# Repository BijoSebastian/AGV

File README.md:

# AGV
Codes for autonomous navigation of ROVER 5 using Beaglebone Black
All modules are written as ROS nodes. PCB design for Beaglebone Black is also provided.
For additional details refer to https://bijosebastian.wordpress.com/mobile-robotics/

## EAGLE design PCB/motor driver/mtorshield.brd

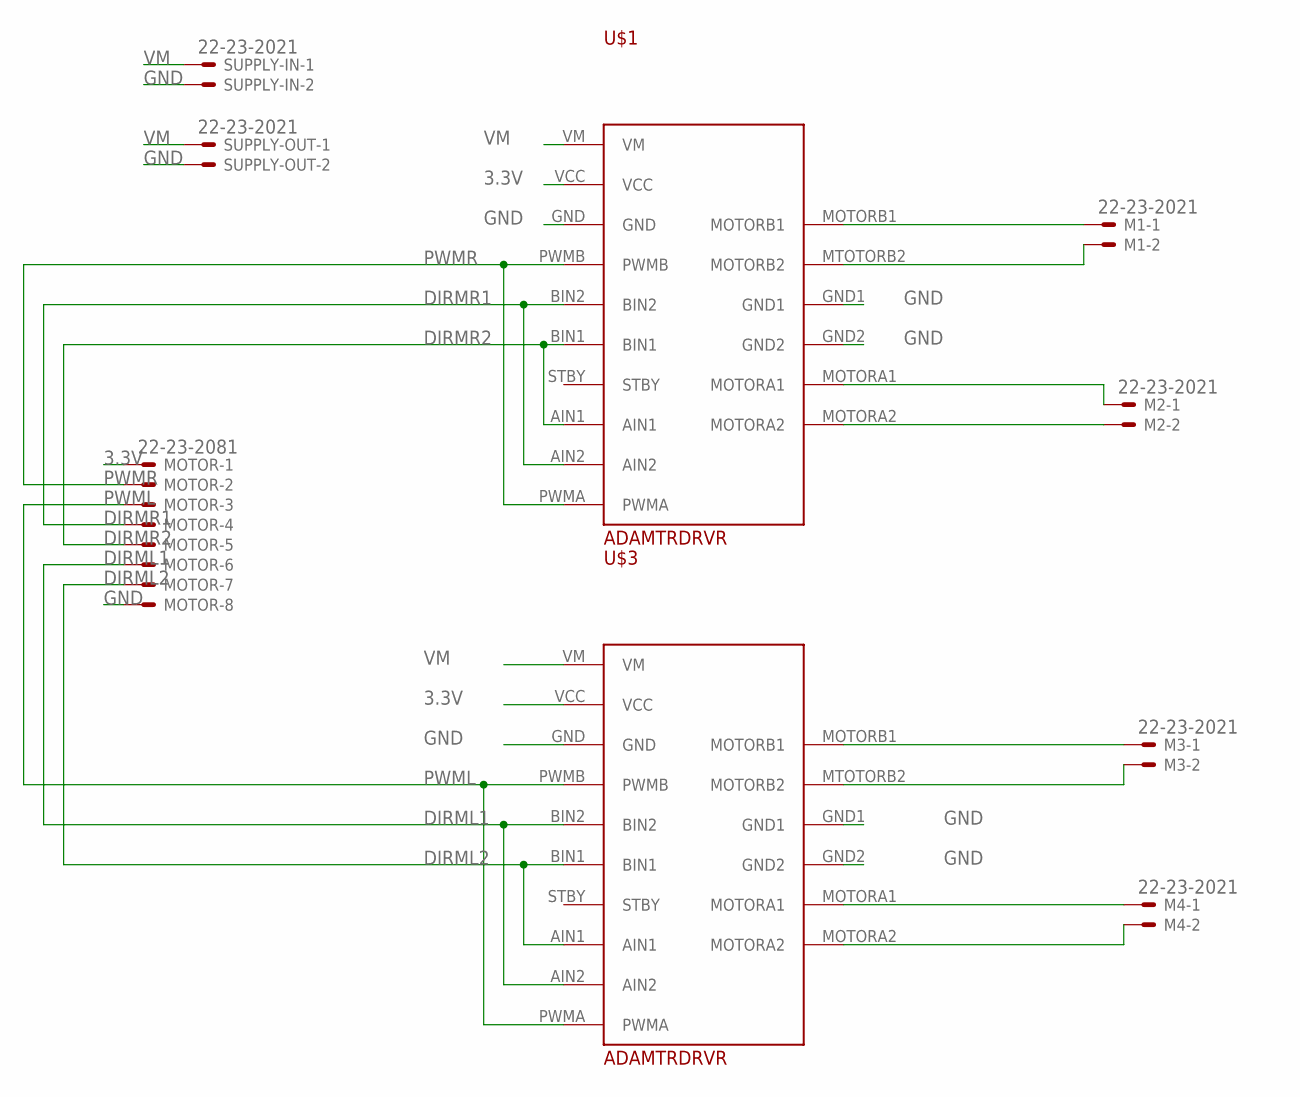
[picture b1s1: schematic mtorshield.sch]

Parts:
M1, M2, M3, M4: 22-23-2021
MOTOR: 22-23-2081
SUPPLY-IN: 22-23-2021
SUPPLY-OUT: 22-23-2021
U$1, U$3: ADAMTRDRVR

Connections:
3.3V: MOTOR.1, U$1.VCC, U$3.VCC
DIRML1: MOTOR.6, U$3.AIN2, U$3.BIN2
DIRML2: MOTOR.7, U$3.AIN1, U$3.BIN1
DIRMR1: MOTOR.4, U$1.AIN2, U$1.BIN2
DIRMR2: MOTOR.5, U$1.AIN1, U$1.BIN1
GND: MOTOR.8, SUPPLY-IN.2, SUPPLY-OUT.2, U$1.GND, U$1.GND1, U$1.GND2, U$3.GND, U$3.GND1, U$3.GND2
unnamed: M1.1, U$1.MOTORB1
unnamed: M1.2, U$1.MTOTORB2 (MOTORB2)
unnamed: M2.1, U$1.MOTORA1
unnamed: M2.2, U$1.MOTORA2
unnamed: M3.1, U$3.MOTORB1
unnamed: M3.2, U$3.MTOTORB2 (MOTORB2)
unnamed: M4.1, U$3.MOTORA1
unnamed: M4.2, U$3.MOTORA2
PWML: MOTOR.3, U$3.PWMA, U$3.PWMB
PWMR: MOTOR.2, U$1.PWMA, U$1.PWMB
VM: SUPPLY-IN.1, SUPPLY-OUT.1, U$1.VM, U$3.VM

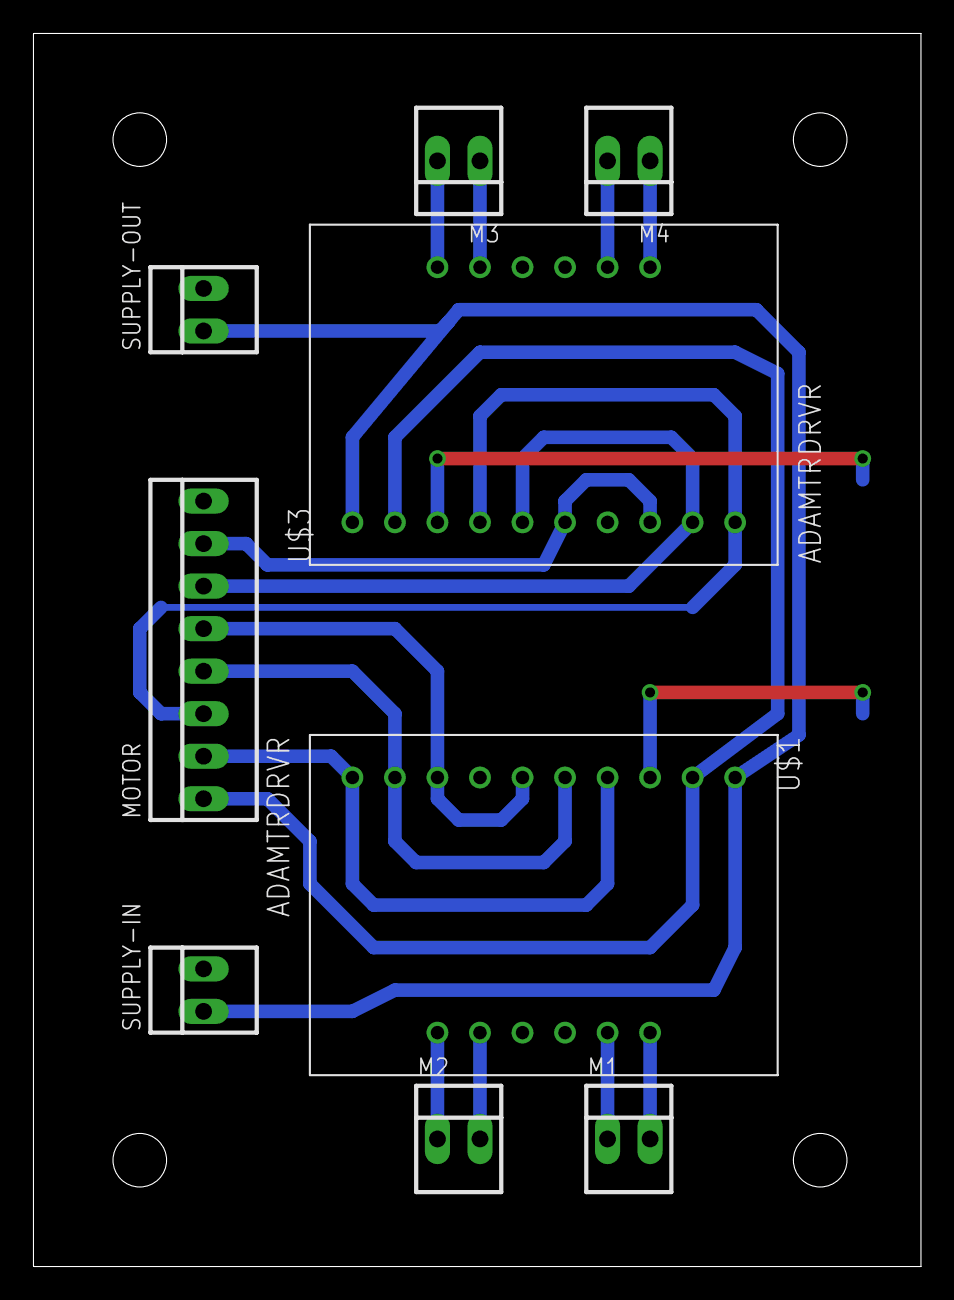
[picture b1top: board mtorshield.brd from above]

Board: 2 copper layers, 53.0 x 73.6 mm, 9 parts (0 on the bottom side), 17 nets.

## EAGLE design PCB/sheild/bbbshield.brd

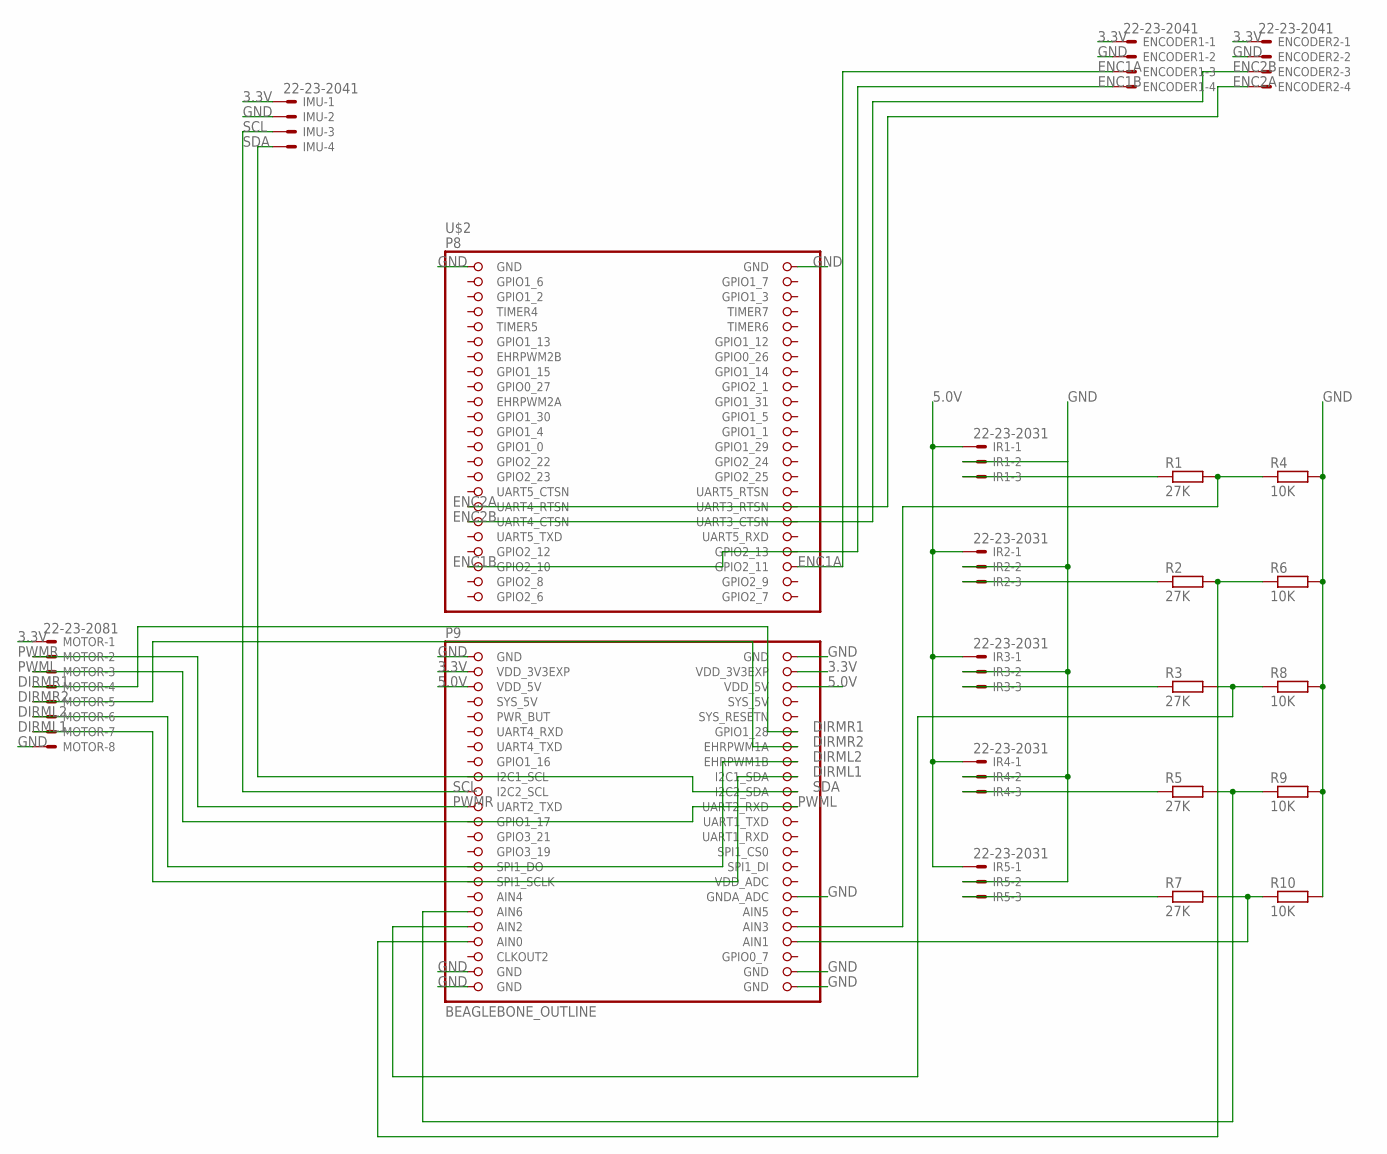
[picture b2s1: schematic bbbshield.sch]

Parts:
ENCODER1, ENCODER2: 22-23-2041
IMU: 22-23-2041
IR1, IR2, IR3, IR4, IR5: 22-23-2031
MOTOR: 22-23-2081
R1, R2, R3, R5, R7: 27K; R0603
R4, R6, R8, R9, R10: 10K; R0603
U$2: BEAGLEBONE_OUTLINE; BEAGLEBONE_SHIELD

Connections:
3.3V: ENCODER1.1, ENCODER2.1, IMU.1, MOTOR.1, U$2.49 (VDD_3V3EXP), U$2.50 (VDD_3V3EXP)
5.0V: IR1.1, IR2.1, IR3.1, IR4.1, IR5.1, U$2.51 (VDD_5V), U$2.52 (VDD_5V)
DIRML1: MOTOR.7, U$2.64 (I2C1_SDA)
DIRML2: MOTOR.6, U$2.62 (EHRPWM1B)
DIRMR1: MOTOR.4, U$2.58 (GPIO1_28)
DIRMR2: MOTOR.5, U$2.60 (EHRPWM1A)
ENC1A: ENCODER1.3, U$2.42 (GPIO2_11)
ENC1B: ENCODER1.4, U$2.41 (GPIO2_10)
ENC2A: ENCODER2.4, U$2.33 (UART4_RTSN)
ENC2B: ENCODER2.3, U$2.35 (UART4_CTSN)
GND: ENCODER1.2, ENCODER2.2, IMU.2, IR1.2, IR2.2, IR3.2, IR4.2, IR5.2, MOTOR.8, R4.2, R6.2, R8.2, R9.2, R10.2, U$2.1 (GND), U$2.2 (GND), U$2.47 (GND), U$2.48 (GND), U$2.80 (GNDA_ADC), U$2.89 (GND), U$2.90 (GND), U$2.91 (GND), U$2.92 (GND)
GPIO1_6: U$2.3 (GPIO1_6)
GPIO1_7: U$2.4 (GPIO1_7)
GPIO2_6: U$2.45 (GPIO2_6)
GPIO2_7: U$2.46 (GPIO2_7)
GPIO2_8: U$2.43 (GPIO2_8)
GPIO2_9: U$2.44 (GPIO2_9)
unnamed: IR1.3, R1.1
unnamed: IR2.3, R2.1
unnamed: IR3.3, R3.1
unnamed: IR4.3, R5.1
unnamed: IR5.3, R7.1
unnamed: R2.2, R6.1, U$2.85 (AIN0)
unnamed: R3.2, R8.1, U$2.83 (AIN2)
unnamed: R1.2, R4.1, U$2.84 (AIN3)
unnamed: R5.2, R9.1, U$2.81 (AIN6)
unnamed: R7.2, R10.1, U$2.86 (AIN1)
PWML: MOTOR.3, U$2.68 (UART2_RXD)
PWMR: MOTOR.2, U$2.67 (UART2_TXD)
SCL: IMU.3, U$2.65 (I2C2_SCL)
SDA: IMU.4, U$2.66 (I2C2_SDA)

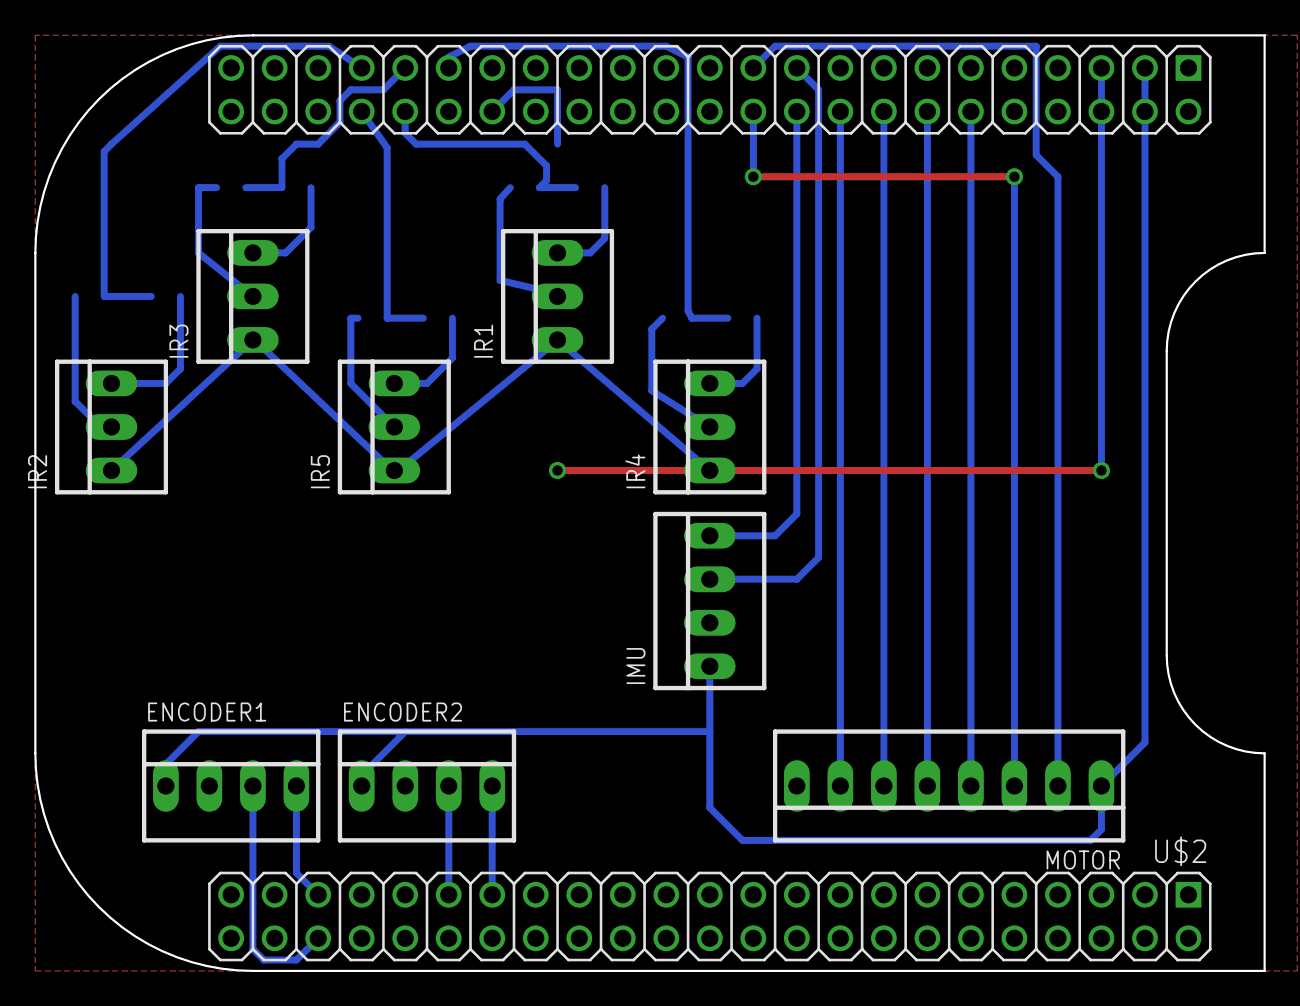
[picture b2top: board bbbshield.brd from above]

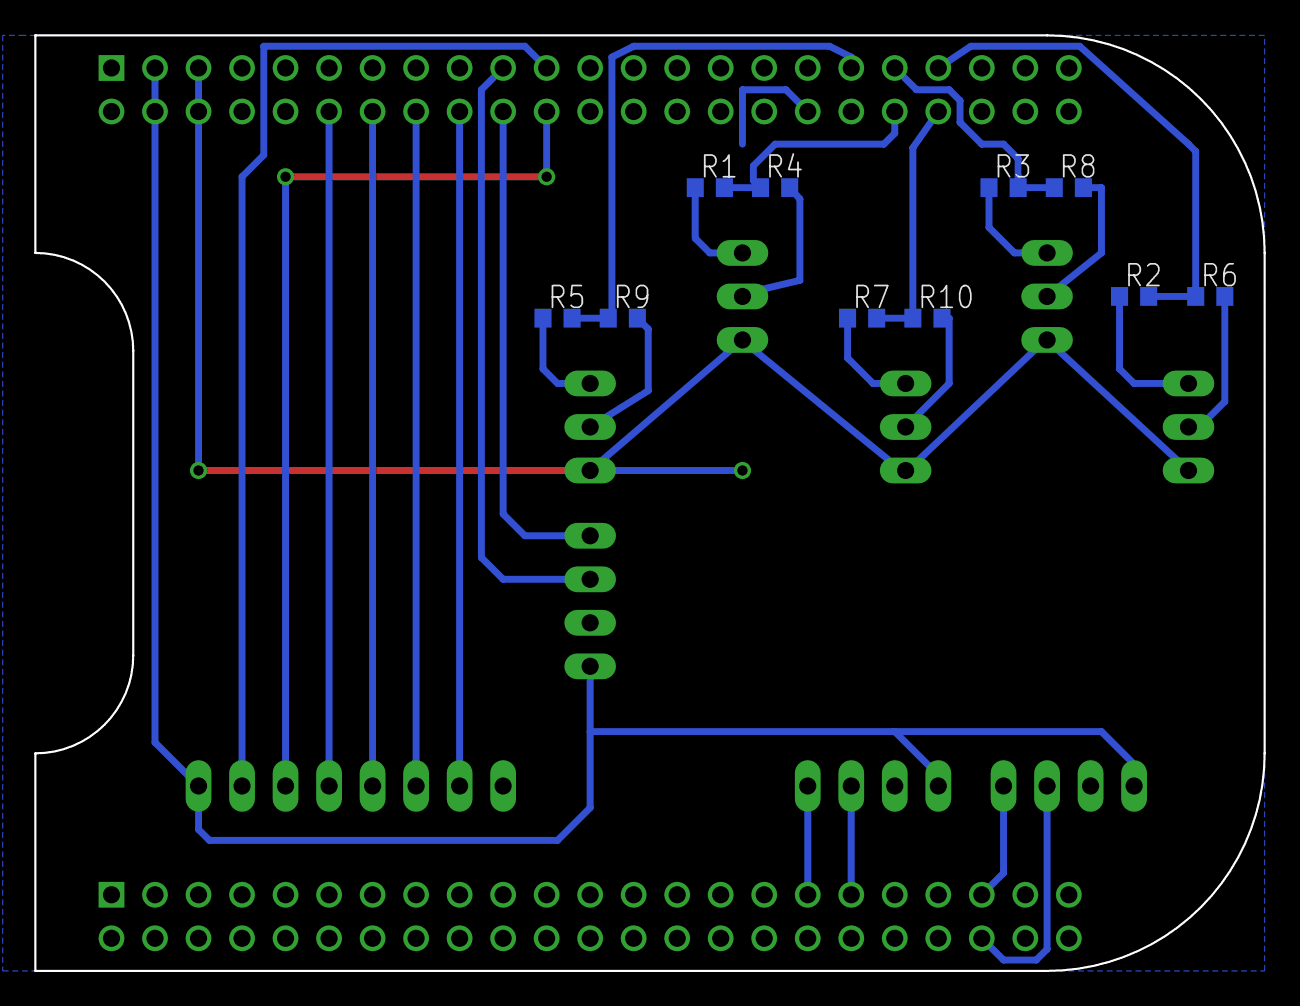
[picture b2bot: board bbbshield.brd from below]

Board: 2 copper layers, 71.8 x 54.6 mm, 20 parts (10 on the bottom side), 25 nets.

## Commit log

2017-12-27 Initial commit.
    See website for description of capabilities.
2017-12-27 The PCB designs for sheild and motor driver
2023-03-26 Create LICENSE
